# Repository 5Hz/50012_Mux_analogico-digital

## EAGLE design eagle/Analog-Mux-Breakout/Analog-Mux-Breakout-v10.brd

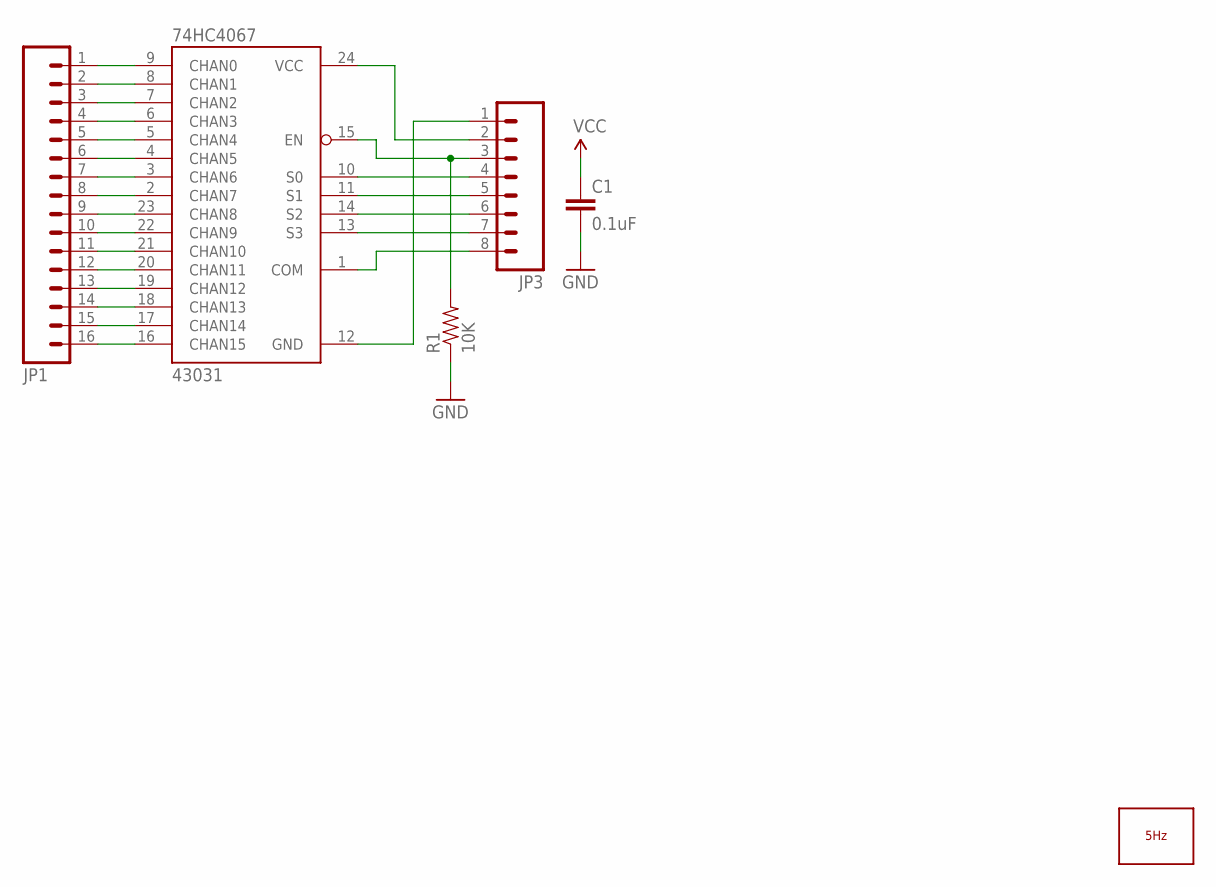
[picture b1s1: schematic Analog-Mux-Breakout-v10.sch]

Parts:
74HC4067: 43031; SSOP24
C1: 0.1uF; C0402
JP1: M16PTH; 1X16
JP3: M08; 1X08
LOGO1: LOGO_5HZ_H_10MM; 5HZ_LOGO_H_10MM
R1: 10K; C0402

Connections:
C0: 74HC4067.9 (CHAN0), JP1.1
C1: 74HC4067.8 (CHAN1), JP1.2
C2: 74HC4067.7 (CHAN2), JP1.3
C3: 74HC4067.6 (CHAN3), JP1.4
C4: 74HC4067.5 (CHAN4), JP1.5
C5: 74HC4067.4 (CHAN5), JP1.6
C6: 74HC4067.3 (CHAN6), JP1.7
C7: 74HC4067.2 (CHAN7), JP1.8
C8: 74HC4067.23 (CHAN8), JP1.9
C9: 74HC4067.22 (CHAN9), JP1.10
C10: 74HC4067.21 (CHAN10), JP1.11
C11: 74HC4067.20 (CHAN11), JP1.12
C12: 74HC4067.19 (CHAN12), JP1.13
C13: 74HC4067.18 (CHAN13), JP1.14
C14: 74HC4067.17 (CHAN14), JP1.15
C15: 74HC4067.16 (CHAN15), JP1.16
EN: 74HC4067.15 (EN), JP3.3, R1.2
GND: 74HC4067.12 (GND), C1.2, JP3.1, R1.1
S0: 74HC4067.10 (S0), JP3.4
S1: 74HC4067.11 (S1), JP3.5
S2: 74HC4067.14 (S2), JP3.6
S3: 74HC4067.13 (S3), JP3.7
SIG: 74HC4067.1 (COM), JP3.8
VCC: 74HC4067.24 (VCC), C1.1, JP3.2

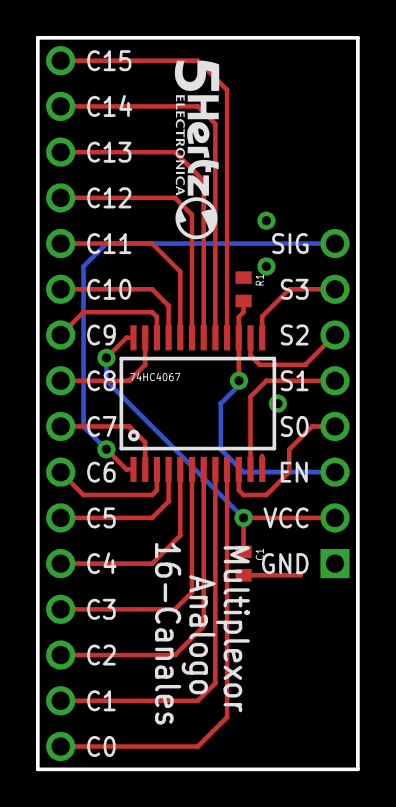
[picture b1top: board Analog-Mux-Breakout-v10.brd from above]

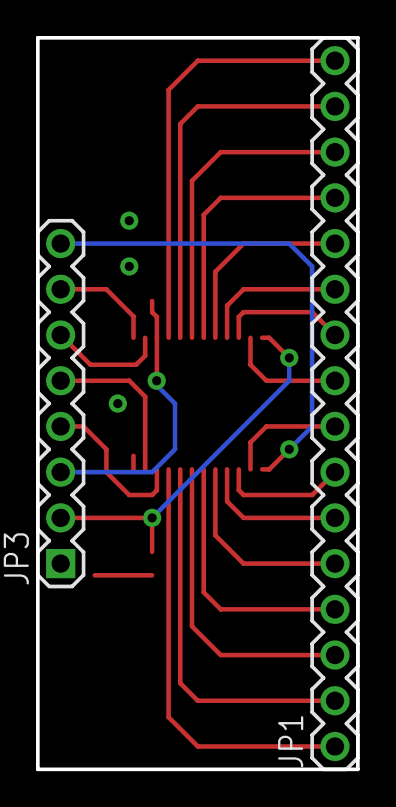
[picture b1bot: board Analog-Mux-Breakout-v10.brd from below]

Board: 2 copper layers, 17.8 x 40.6 mm, 6 parts (2 on the bottom side), 24 nets.

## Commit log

2014-01-09 creación
